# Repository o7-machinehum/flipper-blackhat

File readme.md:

# Flipper Blackhat

The Flipper Blackhat is a Linux based Flipper addon that enables WiFi attacks. It uses an Allwinner A33, which is a quad-core SoC connected to 512MB of RAM. The board has two USB2 ports, and one USB-C, which is connected to an FTDI.

## Software
There are three main repositories for this device.
- [The OS](https://github.com/o7-machinehum/flipper-blackhat-os)
- [The Flipper App](https://github.com/o7-machinehum/flipper-blackhat-app)
- This one (the hardware)

## License
The project is licensed under the Creative Commons (4.0 International License) Attribution—Noncommercial—Share Alike license. This allows sharing and adapting material for non-commercial purposes, provided credit is given to the creator and adaptations are shared under the same terms. The material can be used in any format with necessary technical modifications, but no warranties are provided. The license prohibits imposing additional restrictions and ensures the rights are irrevocable as long as the terms are followed.

Basically... If you make boards for yourself: great, make boards for your friends: great, but **please do not sell hundreds on them on Aliexpress**. I'm selling boards [here](https://shop.rootkitlabs.com/products/flipper-blackhat); the money made here goes back into this project and other similar open-source projects!

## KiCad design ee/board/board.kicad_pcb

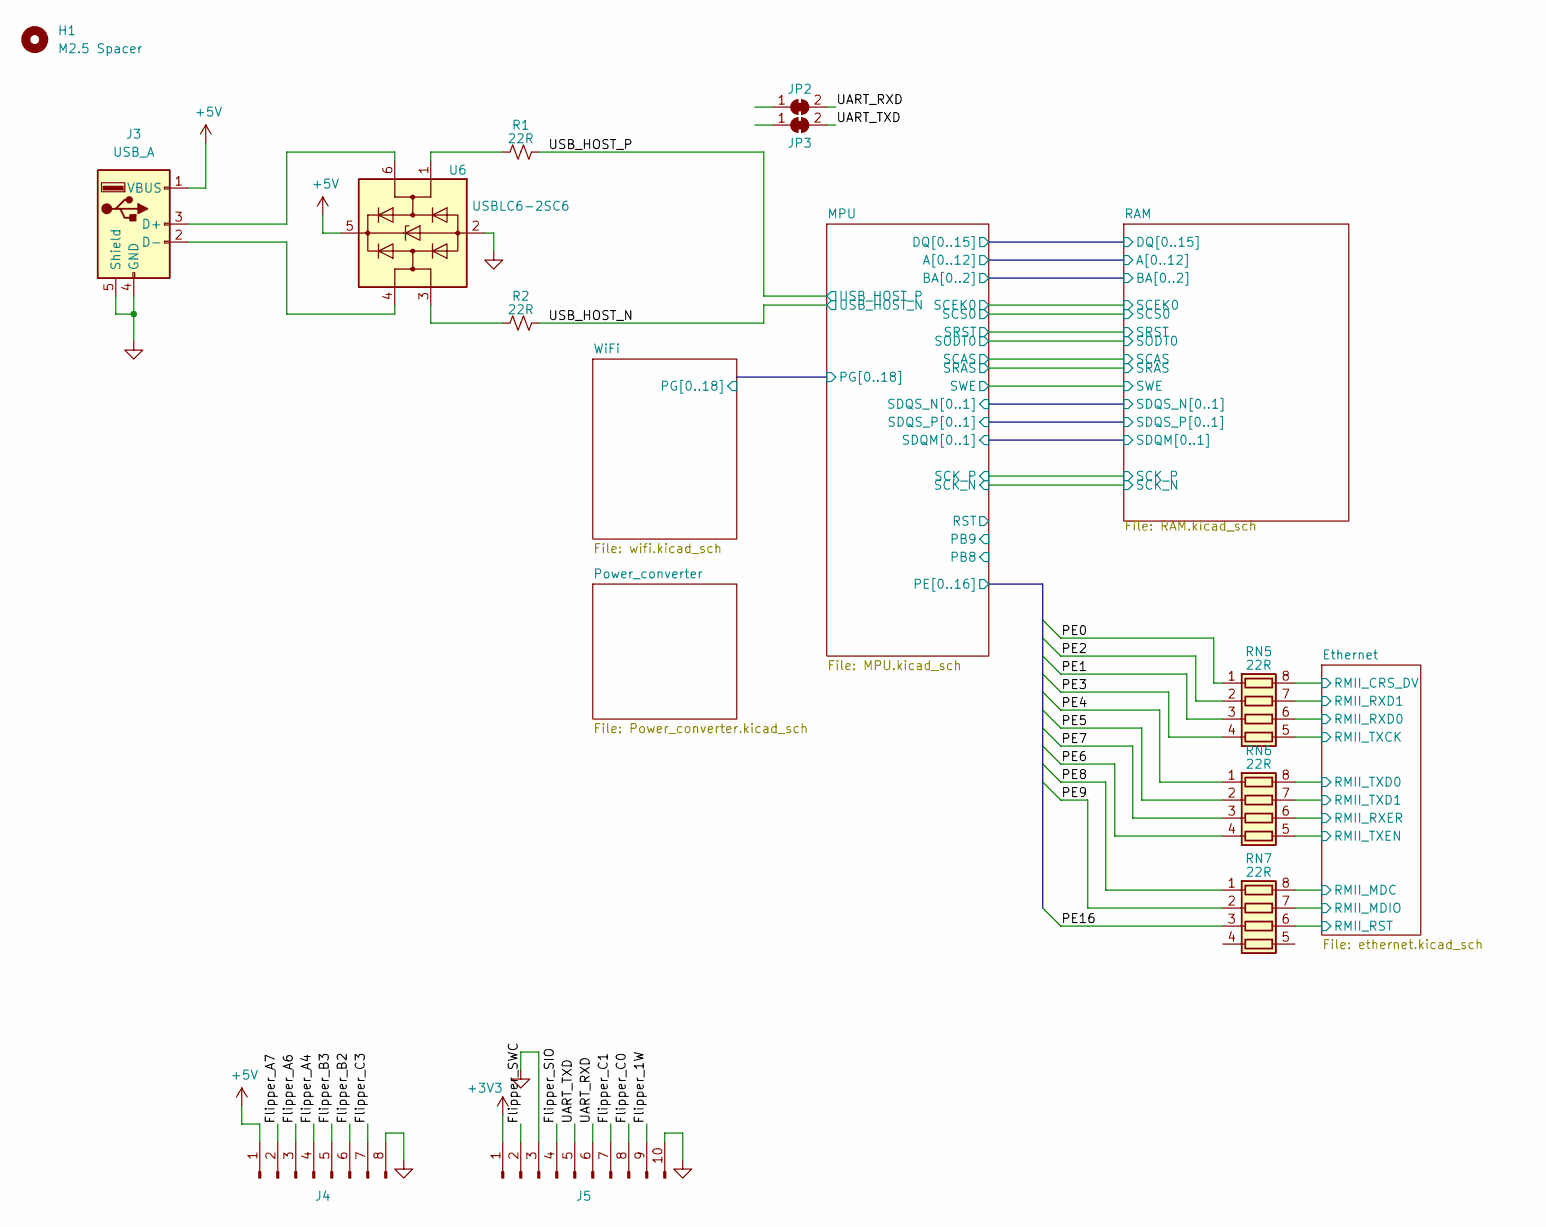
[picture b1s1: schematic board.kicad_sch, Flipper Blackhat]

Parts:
H1: M2.5 Spacer; 9774025151R; MPN 9774025151R
J3: USB_A; USB_A_Receptacle_GCT_USB1046; MPN USB1046-GF-0190-L-B-A
J4: Conn_01x08_Pin; PinHeader_1x08_P2.54mm_Horizontal; MPN PH1RB-08-UA
J5: Conn_01x10_Pin; PinHeader_1x10_P2.54mm_Horizontal; MPN PH1RB-10-UA
JP2, JP3: SolderJumper_2_Bridged; SolderJumper-2_P1.3mm_Bridged2Bar_RoundedPad1.0x1.5mm
R1, R2: 22R; R_0603_1608Metric; MPN RC0603FR-1322RL
RN5, RN6, RN7: 22R; R_Array_Convex_4x0402; MPN 4D02WGJ0220TCE
U6: USBLC6-2SC6; SOT-23-6; MPN USBLC6-2SC6

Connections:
+3V3: J5.1; also elsewhere on the board
+5V: J3.1 (VBUS), J4.1, U6.5 (VBUS); also elsewhere on the board
/Ethernet/RMII_CRS_DV: RN5.8 (R1.2); also elsewhere on the board
/Ethernet/RMII_MDC: RN7.8 (R1.2); also elsewhere on the board
/Ethernet/RMII_MDIO: RN7.7 (R2.2); also elsewhere on the board
/Ethernet/RMII_RXD0: RN5.6 (R3.2); also elsewhere on the board
/Ethernet/RMII_RXD1: RN5.7 (R2.2); also elsewhere on the board
/Ethernet/RMII_RXER: RN6.6 (R3.2); also elsewhere on the board
/Ethernet/RMII_TXCK: RN5.5 (R4.2); also elsewhere on the board
/Ethernet/RMII_TXD0: RN6.8 (R1.2); also elsewhere on the board
/Ethernet/RMII_TXD1: RN6.7 (R2.2); also elsewhere on the board
/Ethernet/RMII_TXEN: RN6.5 (R4.2); also elsewhere on the board
/Ethernet/RST: RN7.6 (R3.2); also elsewhere on the board
/Flipper_1W: J5.9
/Flipper_A4: J4.4
/Flipper_A6: J4.3
/Flipper_A7: J4.2
/Flipper_B2: J4.6
/Flipper_B3: J4.5
/Flipper_C0: J5.8
/Flipper_C1: J5.7
/Flipper_C3: J4.7
/Flipper_SIO: J5.4
/Flipper_SWC: J5.2
/MPU/PE0: RN5.1 (R1.1); also elsewhere on the board
/MPU/PE1: RN5.3 (R3.1); also elsewhere on the board
/MPU/PE2: RN5.2 (R2.1); also elsewhere on the board
/MPU/PE3: RN5.4 (R4.1); also elsewhere on the board
/MPU/PE4: RN6.1 (R1.1); also elsewhere on the board
/MPU/PE5: RN6.2 (R2.1); also elsewhere on the board
/MPU/PE6: RN6.4 (R4.1); also elsewhere on the board
/MPU/PE7: RN6.3 (R3.1); also elsewhere on the board
/MPU/PE8: RN7.1 (R1.1); also elsewhere on the board
/MPU/PE9: RN7.2 (R2.1); also elsewhere on the board
/MPU/PE16: RN7.3 (R3.1); also elsewhere on the board
/UART_RXD: J5.6, JP2.2 (B)
/UART_TXD: J5.5, JP3.2 (B)
/USB_HOST_N: R2.2; also elsewhere on the board
/USB_HOST_P: R1.2; also elsewhere on the board
GND: J3.4 (GND), J3.5 (Shield), J4.8, J5.3, J5.10, U6.2 (GND); also elsewhere on the board
unnamed: J3.3 (D+), U6.6 (I/O1)
unnamed: J3.2 (D-), U6.4 (I/O2)
unnamed: R1.1, U6.1 (I/O1)
unnamed: R2.1, U6.3 (I/O2)

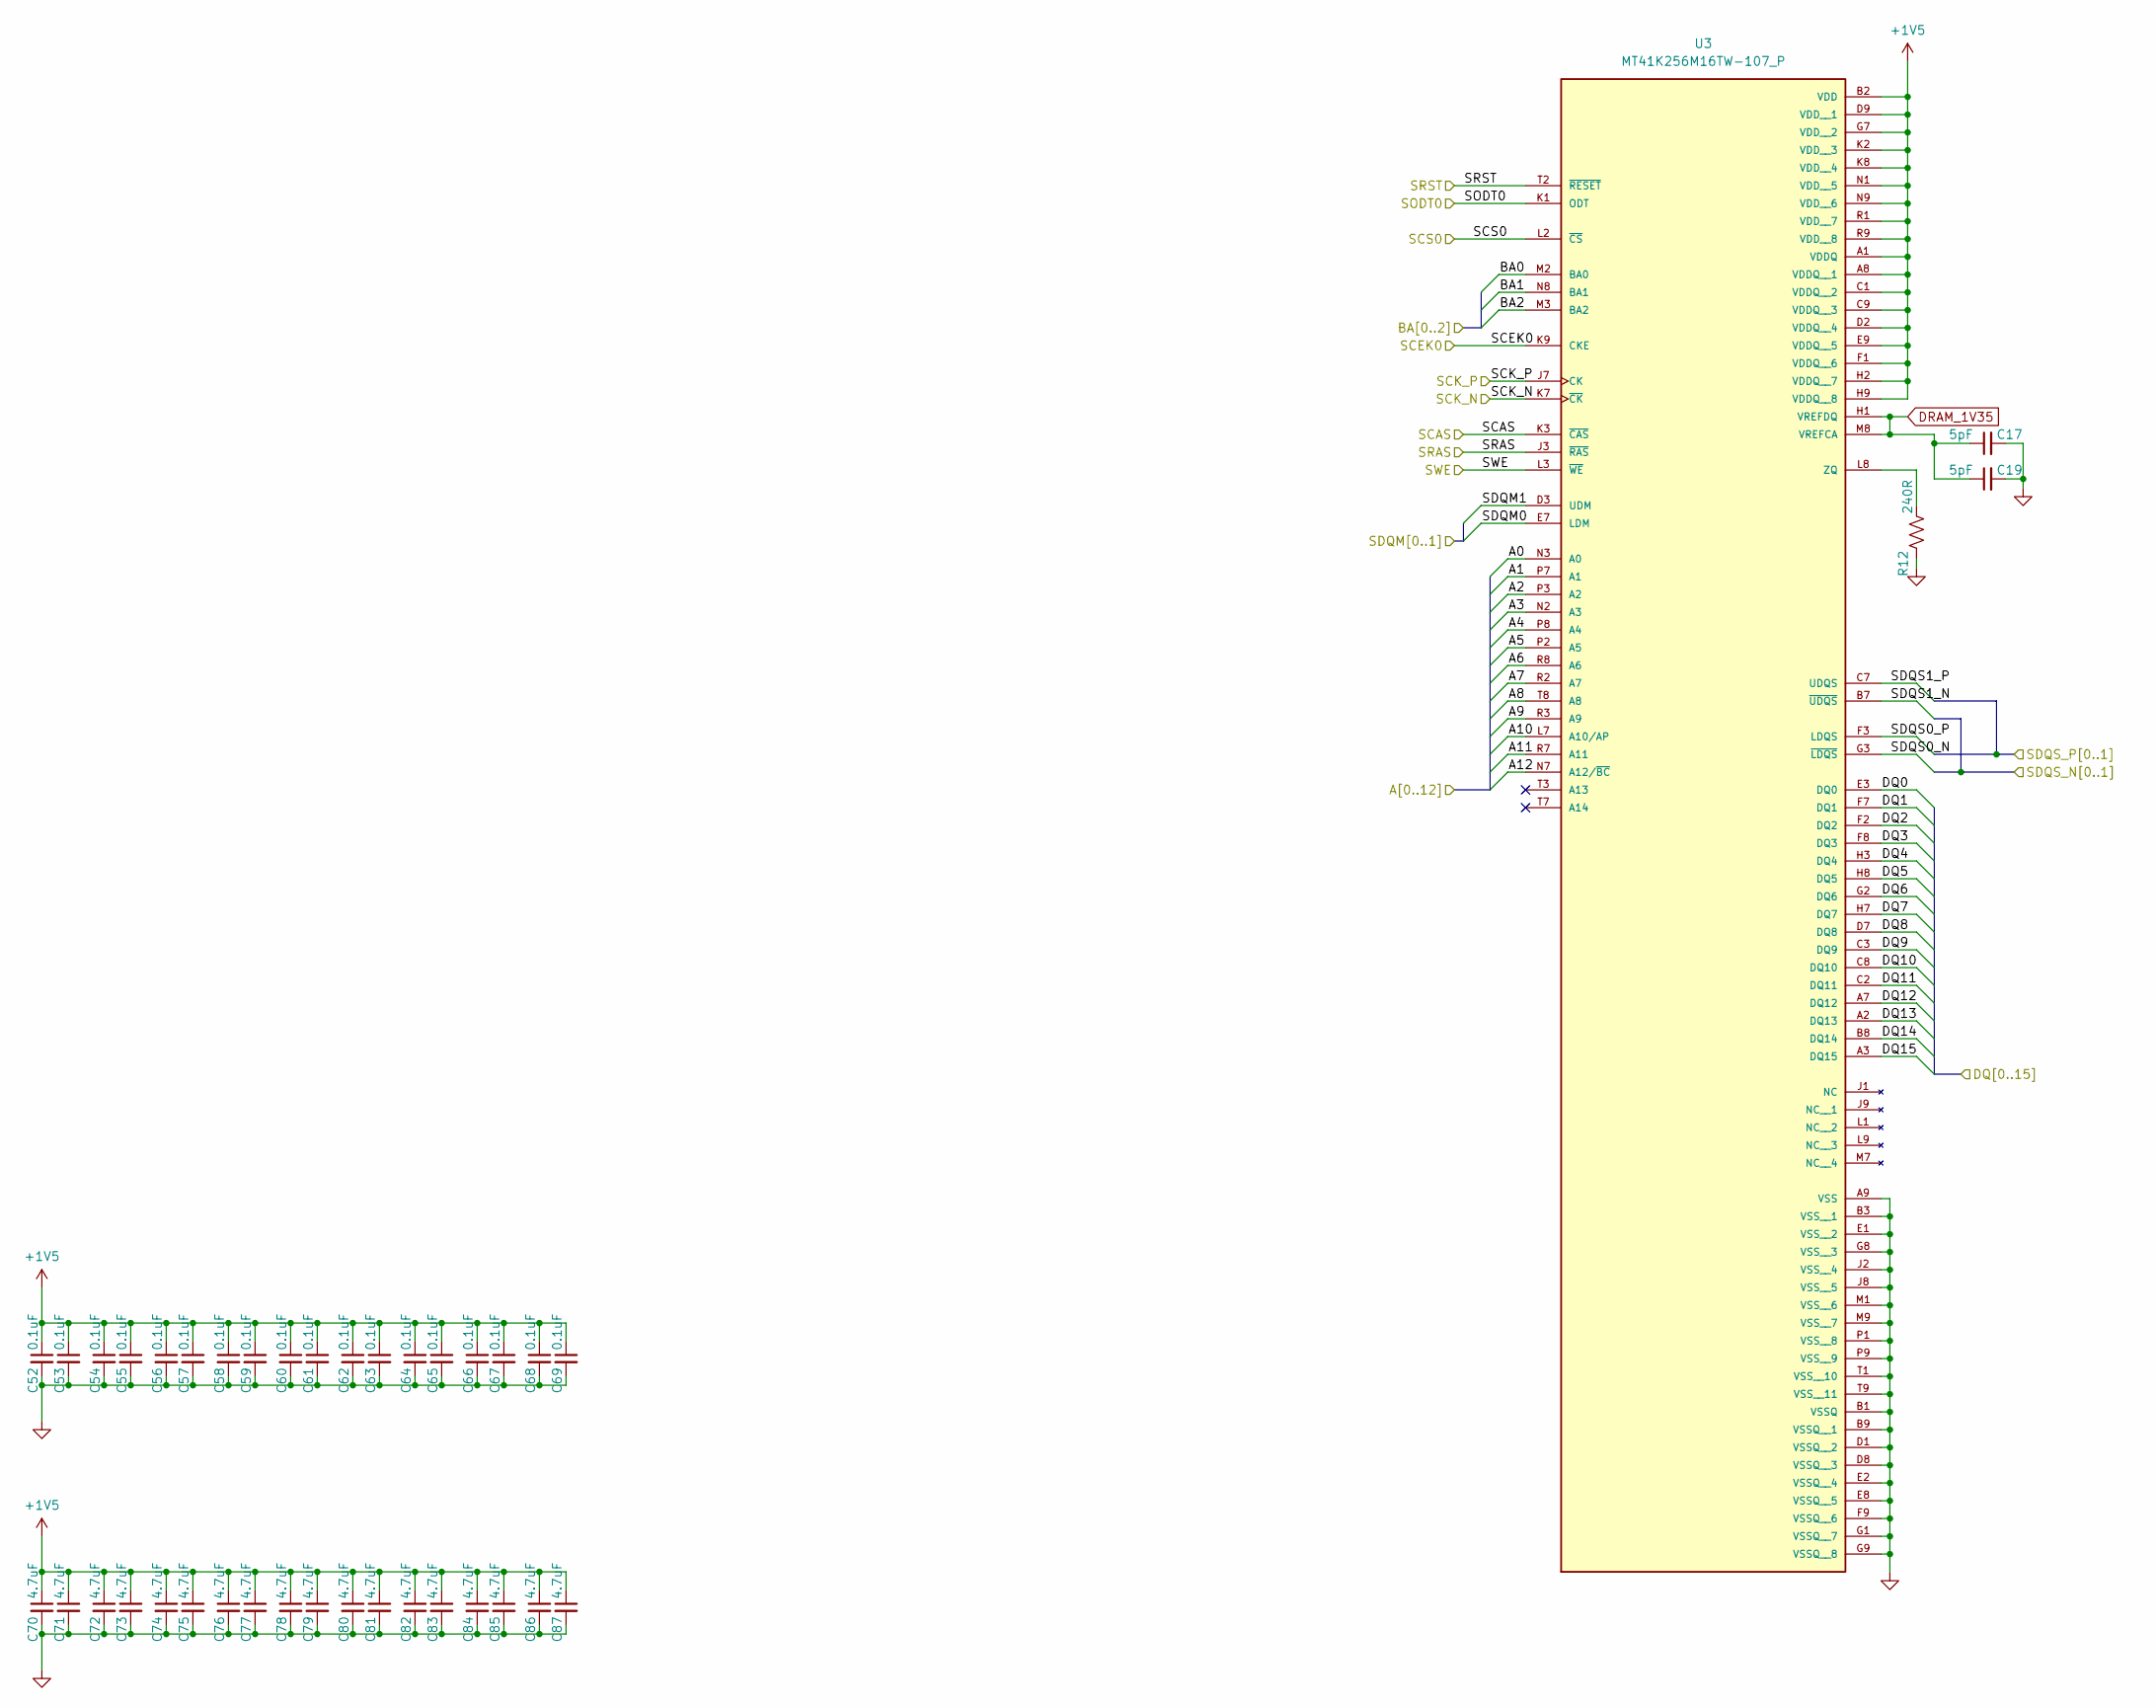
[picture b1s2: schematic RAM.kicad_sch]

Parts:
C17, C19: 5PF 50V C0G/NP0 0603; C_0603_1608Metric; MPN CL10C050CB81PNC
C52, C53, C54, C55, C56, C57, C58, C59, C60, C61, C62, C63, C64, C65, C66, C67, C68, C69: 16V 0.1uF X7R 0402; C_0402_1005Metric; MPN MLASE105SB7104KFNA01
C70, C71, C72, C73, C74, C75, C76, C77, C78, C79, C80, C81, C82, C83, C84, C85, C86, C87: 4.7 uF 16V 0805 X7R; C_0402_1005Metric; MPN C0805C475K4RACAUTO
R12: 240R; R_0603_1608Metric; MPN CRCW0603240RFKEAC
U3: MT41K256M16TW-107_P; BGA96C80P9X16_1400X800X120; PARTREV P

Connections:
+1V5: C52.1, C53.1, C54.1, C55.1, C56.1, C57.1, C58.1, C59.1, C60.1, C61.1, C62.1, C63.1, C64.1, C65.1, C66.1, C67.1, C68.1, C69.1, C70.1, C71.1, C72.1, C73.1, C74.1, C75.1, C76.1, C77.1, C78.1, C79.1, C80.1, C81.1, C82.1, C83.1, C84.1, C85.1, C86.1, C87.1, U3.A1 (VDDQ), U3.A8 (VDDQ__1), U3.B2 (VDD), U3.C1 (VDDQ__2), U3.C9 (VDDQ__3), U3.D2 (VDDQ__4), U3.D9 (VDD__1), U3.E9 (VDDQ__5), U3.F1 (VDDQ__6), U3.G7 (VDD__2), U3.H2 (VDDQ__7), U3.H9 (VDDQ__8), U3.K2 (VDD__3), U3.K8 (VDD__4), U3.N1 (VDD__5), U3.N9 (VDD__6), U3.R1 (VDD__7), U3.R9 (VDD__8); also elsewhere on the board
/MPU/A0: U3.N3 (A0); also elsewhere on the board
/MPU/A1: U3.P7 (A1); also elsewhere on the board
/MPU/A2: U3.P3 (A2); also elsewhere on the board
/MPU/A3: U3.N2 (A3); also elsewhere on the board
/MPU/A4: U3.P8 (A4); also elsewhere on the board
/MPU/A5: U3.P2 (A5); also elsewhere on the board
/MPU/A6: U3.R8 (A6); also elsewhere on the board
/MPU/A7: U3.R2 (A7); also elsewhere on the board
/MPU/A8: U3.T8 (A8); also elsewhere on the board
/MPU/A9: U3.R3 (A9); also elsewhere on the board
/MPU/A10: U3.L7 (A10/AP); also elsewhere on the board
/MPU/A11: U3.R7 (A11); also elsewhere on the board
/MPU/A12: U3.N7 (A12/~BC); also elsewhere on the board
/MPU/BA0: U3.M2 (BA0); also elsewhere on the board
/MPU/BA1: U3.N8 (BA1); also elsewhere on the board
/MPU/BA2: U3.M3 (BA2); also elsewhere on the board
/MPU/DQ0: U3.E3 (DQ0); also elsewhere on the board
/MPU/DQ1: U3.F7 (DQ1); also elsewhere on the board
/MPU/DQ2: U3.F2 (DQ2); also elsewhere on the board
/MPU/DQ3: U3.F8 (DQ3); also elsewhere on the board
/MPU/DQ4: U3.H3 (DQ4); also elsewhere on the board
/MPU/DQ5: U3.H8 (DQ5); also elsewhere on the board
/MPU/DQ6: U3.G2 (DQ6); also elsewhere on the board
/MPU/DQ7: U3.H7 (DQ7); also elsewhere on the board
/MPU/DQ8: U3.D7 (DQ8); also elsewhere on the board
/MPU/DQ9: U3.C3 (DQ9); also elsewhere on the board
/MPU/DQ10: U3.C8 (DQ10); also elsewhere on the board
/MPU/DQ11: U3.C2 (DQ11); also elsewhere on the board
/MPU/DQ12: U3.A7 (DQ12); also elsewhere on the board
/MPU/DQ13: U3.A2 (DQ13); also elsewhere on the board
/MPU/DQ14: U3.B8 (DQ14); also elsewhere on the board
/MPU/DQ15: U3.A3 (DQ15); also elsewhere on the board
/MPU/SCAS: U3.K3 (~CAS); also elsewhere on the board
/MPU/SCEK0: U3.K9 (CKE); also elsewhere on the board
/MPU/SCK_N: U3.K7 (~CK); also elsewhere on the board
/MPU/SCK_P: U3.J7 (CK); also elsewhere on the board
/MPU/SCS0: U3.L2 (~CS); also elsewhere on the board
/MPU/SDQM0: U3.E7 (LDM); also elsewhere on the board
/MPU/SDQM1: U3.D3 (UDM); also elsewhere on the board
/MPU/SODT0: U3.K1 (ODT); also elsewhere on the board
/MPU/SRAS: U3.J3 (~RAS); also elsewhere on the board
/MPU/SRST: U3.T2 (~RESET); also elsewhere on the board
/MPU/SWE: U3.L3 (~WE); also elsewhere on the board
/RAM/SDQS0_N: U3.G3 (~LDQS)
/RAM/SDQS0_P: U3.F3 (LDQS)
/RAM/SDQS1_N: U3.B7 (~UDQS)
/RAM/SDQS1_P: U3.C7 (UDQS)
DRAM_1V35: C17.1, C19.1, U3.H1 (VREFDQ), U3.M8 (VREFCA); also elsewhere on the board
GND: C17.2, C19.2, C52.2, C53.2, C54.2, C55.2, C56.2, C57.2, C58.2, C59.2, C60.2, C61.2, C62.2, C63.2, C64.2, C65.2, C66.2, C67.2, C68.2, C69.2, C70.2, C71.2, C72.2, C73.2, C74.2, C75.2, C76.2, C77.2, C78.2, C79.2, C80.2, C81.2, C82.2, C83.2, C84.2, C85.2, C86.2, C87.2, R12.1, U3.A9 (VSS), U3.B1 (VSSQ), U3.B3 (VSS__1), U3.B9 (VSSQ__1), U3.D1 (VSSQ__2), U3.D8 (VSSQ__3), U3.E1 (VSS__2), U3.E2 (VSSQ__4), U3.E8 (VSSQ__5), U3.F9 (VSSQ__6), U3.G1 (VSSQ__7), U3.G8 (VSS__3), U3.G9 (VSSQ__8), U3.J2 (VSS__4), U3.J8 (VSS__5), U3.M1 (VSS__6), U3.M9 (VSS__7), U3.P1 (VSS__8), U3.P9 (VSS__9), U3.T1 (VSS__10), U3.T9 (VSS__11); also elsewhere on the board
unnamed: R12.2, U3.L8 (ZQ)

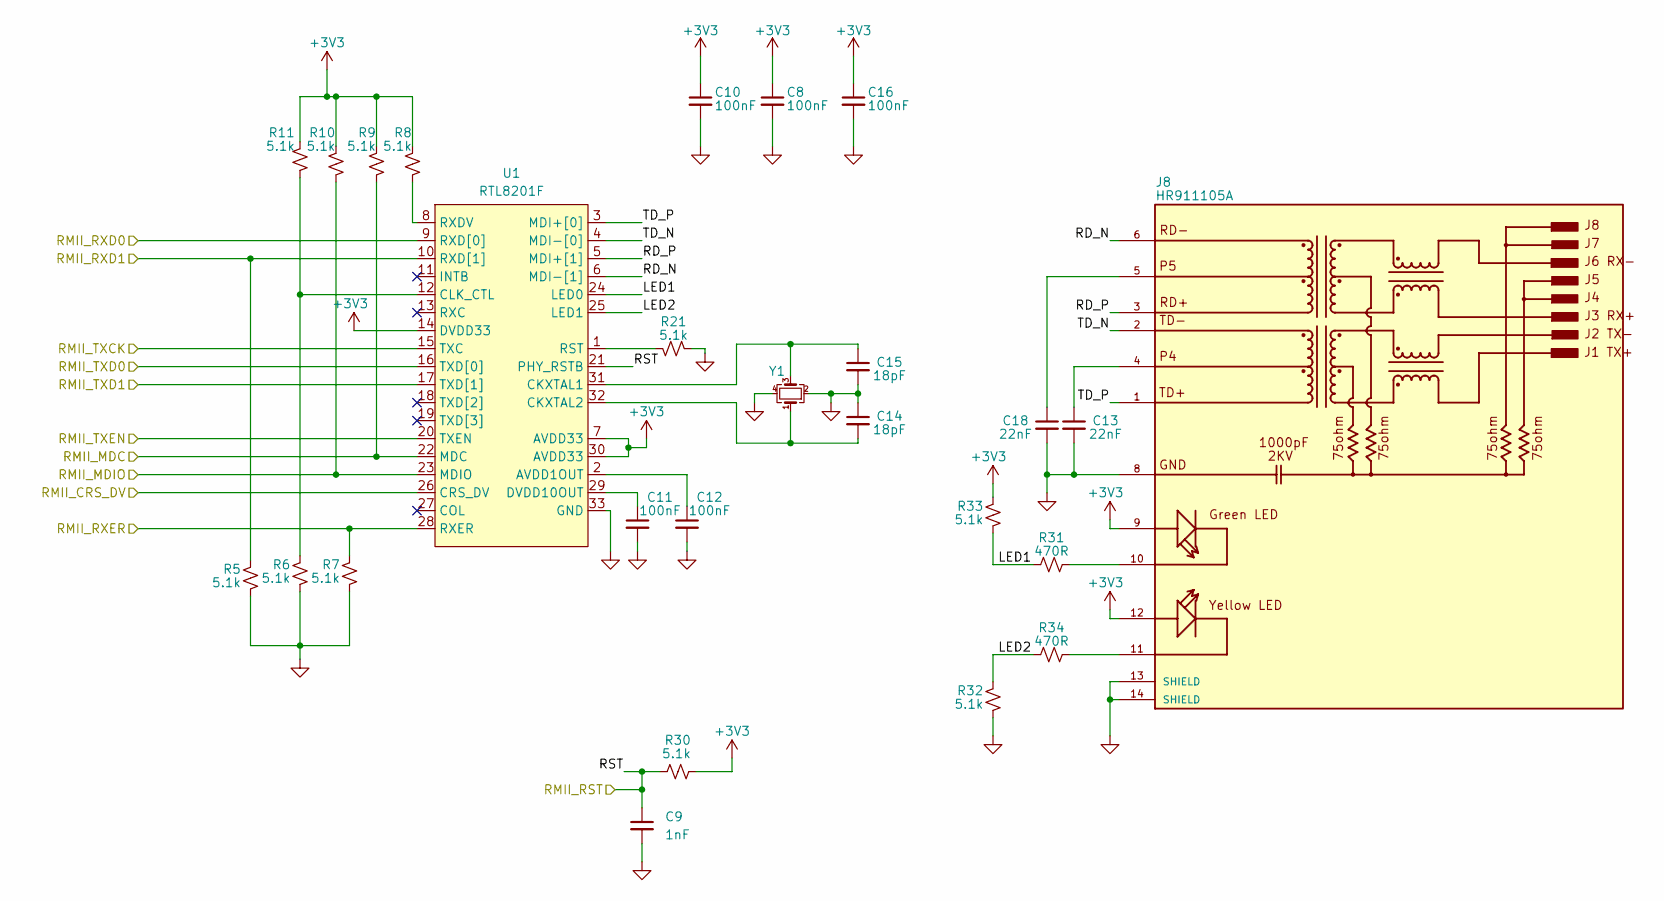
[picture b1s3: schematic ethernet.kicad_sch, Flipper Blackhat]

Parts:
C8, C10, C11, C12, C16: 100nF; C_0603_1608Metric; MPN CC0603KRX7R7BB104
C9: 1nF; C_0603_1608Metric; MPN CC0603KRX7R7BB102
C13, C18: 22nF; C_0603_1608Metric; MPN CC0603KRX7R7BB223
C14, C15: 18pF; C_0603_1608Metric; MPN CC0603JPNPO9BN180
J8: HR911105A; HR911105a; MPN HR911105A
R5, R6, R7, R8, R9, R10, R11, R21, R30, R32, R33: 5.1k; R_0603_1608Metric; MPN RC0603FR-135K1L
R31, R34: 470R; R_0603_1608Metric; MPN RC0603FR-13470KL
U1: RTL8201F; QFN-32-1EP_5x5mm_P0.5mm_EP3.3x3.3mm; MPN RTL8201F
Y1: Crystal_GND24_Small; Crystal_SMD_3225-4Pin_3.2x2.5mm; MPN 7M25000033

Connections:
+3V3: C8.1, C10.1, C16.1, J8.9, J8.12, R8.2, R9.2, R10.2, R11.2, R30.1, R33.2, U1.7 (AVDD33), U1.14 (DVDD33), U1.30 (AVDD33); also elsewhere on the board
/Ethernet/LED1: R31.2, R33.1, U1.24 (LED0)
/Ethernet/LED2: R32.2, R34.2, U1.25 (LED1)
/Ethernet/RD_N: J8.6, U1.6 (MDI-[1])
/Ethernet/RD_P: J8.3, U1.5 (MDI+[1])
/Ethernet/RMII_CRS_DV: U1.26 (CRS_DV); also elsewhere on the board
/Ethernet/RMII_MDC: R9.1, U1.22 (MDC); also elsewhere on the board
/Ethernet/RMII_MDIO: R10.1, U1.23 (MDIO); also elsewhere on the board
/Ethernet/RMII_RXD0: U1.9 (RXD[0]); also elsewhere on the board
/Ethernet/RMII_RXD1: R5.2, U1.10 (RXD[1]); also elsewhere on the board
/Ethernet/RMII_RXER: R7.2, U1.28 (RXER); also elsewhere on the board
/Ethernet/RMII_TXCK: U1.15 (TXC); also elsewhere on the board
/Ethernet/RMII_TXD0: U1.16 (TXD[0]); also elsewhere on the board
/Ethernet/RMII_TXD1: U1.17 (TXD[1]); also elsewhere on the board
/Ethernet/RMII_TXEN: U1.20 (TXEN); also elsewhere on the board
/Ethernet/RST: C9.1, R30.2, U1.21 (PHY_RSTB); also elsewhere on the board
/Ethernet/TD_N: J8.2, U1.4 (MDI-[0])
/Ethernet/TD_P: J8.1, U1.3 (MDI+[0])
GND: C8.2, C9.2, C10.2, C11.2, C12.2, C13.2, C14.1, C15.2, C16.2, C18.2, J8.8, J8.13 (SHIELD), J8.14 (SHIELD), R5.1, R6.1, R7.1, R21.2, R32.1, U1.33 (GND), Y1.2, Y1.4; also elsewhere on the board
unnamed: C13.1, J8.4
unnamed: C18.1, J8.5
unnamed: J8.10, R31.1
unnamed: J8.11, R34.1
unnamed: C12.1, U1.2 (AVDD1OUT)
unnamed: C15.1, U1.31 (CKXTAL1), Y1.3
unnamed: C14.2, U1.32 (CKXTAL2), Y1.1
unnamed: R6.2, R11.1, U1.12 (CLK_CTL)
unnamed: C11.1, U1.29 (DVDD10OUT)
unnamed: R21.1, U1.1 (RST)
unnamed: R8.1, U1.8 (RXDV)

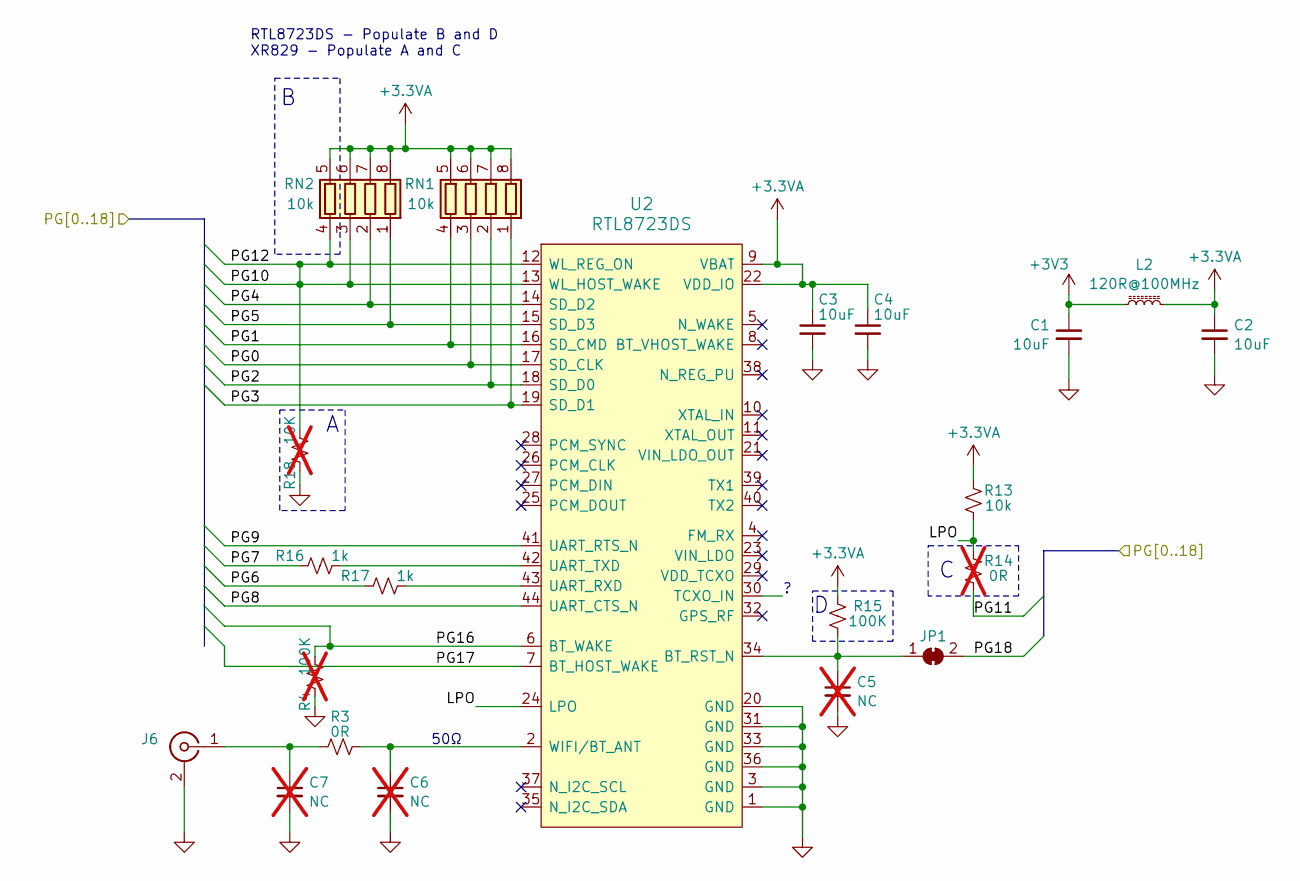
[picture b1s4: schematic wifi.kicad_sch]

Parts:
C1, C2, C3, C4: 10uF; C_0603_1608Metric; MPN LMK107BBJ106MALT
C5, C6, C7: NC; C_0603_1608Metric; not fitted
J6: Conn_Coaxial; SMA_Amphenol_901-143_Horizontal; MPN 901-143-6RFX
JP1: SolderJumper_2_Bridged; SolderJumper-2_P1.3mm_Bridged2Bar_RoundedPad1.0x1.5mm
L2: 120R@100MHz; R_0805_2012Metric; MPN MMZ2012R121AT000
R3: 0R; R_0603_1608Metric; MPN RC0603FR-130RL
R4: 100K; R_0603_1608Metric; not fitted
R13: 10k; R_0603_1608Metric; MPN RC0603FR-1310KL
R14: 0R; R_0603_1608Metric; not fitted
R15: 100K; R_0603_1608Metric; MPN RC0603FR-13100KL
R16, R17: 1k; R_0603_1608Metric; MPN RC0603FR-131KL
R18: 10K; R_0603_1608Metric; not fitted
RN1, RN2: 10k; R_Array_Convex_4x0402; MPN 4D02WGJ0103TCE
U2: RTL8723DS; RTL8723; MPN RTL8723DS

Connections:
+3.3VA: C2.1, C3.1, C4.1, L2.2, R13.2, R15.2, RN1.5 (R4.2), RN1.6 (R3.2), RN1.7 (R2.2), RN1.8 (R1.2), RN2.5 (R4.2), RN2.6 (R3.2), RN2.7 (R2.2), RN2.8 (R1.2), U2.9 (VBAT), U2.22 (VDD_IO)
+3V3: C1.1, L2.1; also elsewhere on the board
/WiFi/LPO: R13.1, R14.2, U2.24 (LPO)
/WiFi/PG0: RN1.3 (R3.1), U2.17 (SD_CLK)
/WiFi/PG1: RN1.4 (R4.1), U2.16 (SD_CMD)
/WiFi/PG2: RN1.2 (R2.1), U2.18 (SD_D0)
/WiFi/PG3: RN1.1 (R1.1), U2.19 (SD_D1)
/WiFi/PG4: RN2.2 (R2.1), U2.14 (SD_D2)
/WiFi/PG5: RN2.1 (R1.1), U2.15 (SD_D3)
/WiFi/PG6: R17.1
/WiFi/PG7: R16.1
/WiFi/PG8: U2.44 (UART_CTS_N)
/WiFi/PG9: U2.41 (UART_RTS_N)
/WiFi/PG10: R18.2, RN2.3 (R3.1), RN2.4 (R4.1), U2.12 (WL_REG_ON), U2.13 (WL_HOST_WAKE)
/WiFi/PG11: R14.1
/WiFi/PG16: R4.2, U2.6 (BT_WAKE)
/WiFi/PG17: U2.7 (BT_HOST_WAKE)
/WiFi/PG18: JP1.2 (B)
GND: C1.2, C2.2, C3.2, C4.2, C5.2, C6.2, C7.2, J6.2 (Ext), R4.1, R18.1, U2.1 (GND), U2.3 (GND), U2.20 (GND), U2.31 (GND), U2.33 (GND), U2.36 (GND); also elsewhere on the board
unnamed: C7.1, J6.1 (In), R3.1
unnamed: C5.1, JP1.1 (A), R15.1, U2.34 (BT_RST_N)
unnamed: R17.2, U2.43 (UART_RXD)
unnamed: R16.2, U2.42 (UART_TXD)
unnamed: C6.1, R3.2, U2.2 (WIFI/BT_ANT)

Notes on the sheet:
RTL8723DS - Populate B and D XR829 - Populate A and C
50Ω

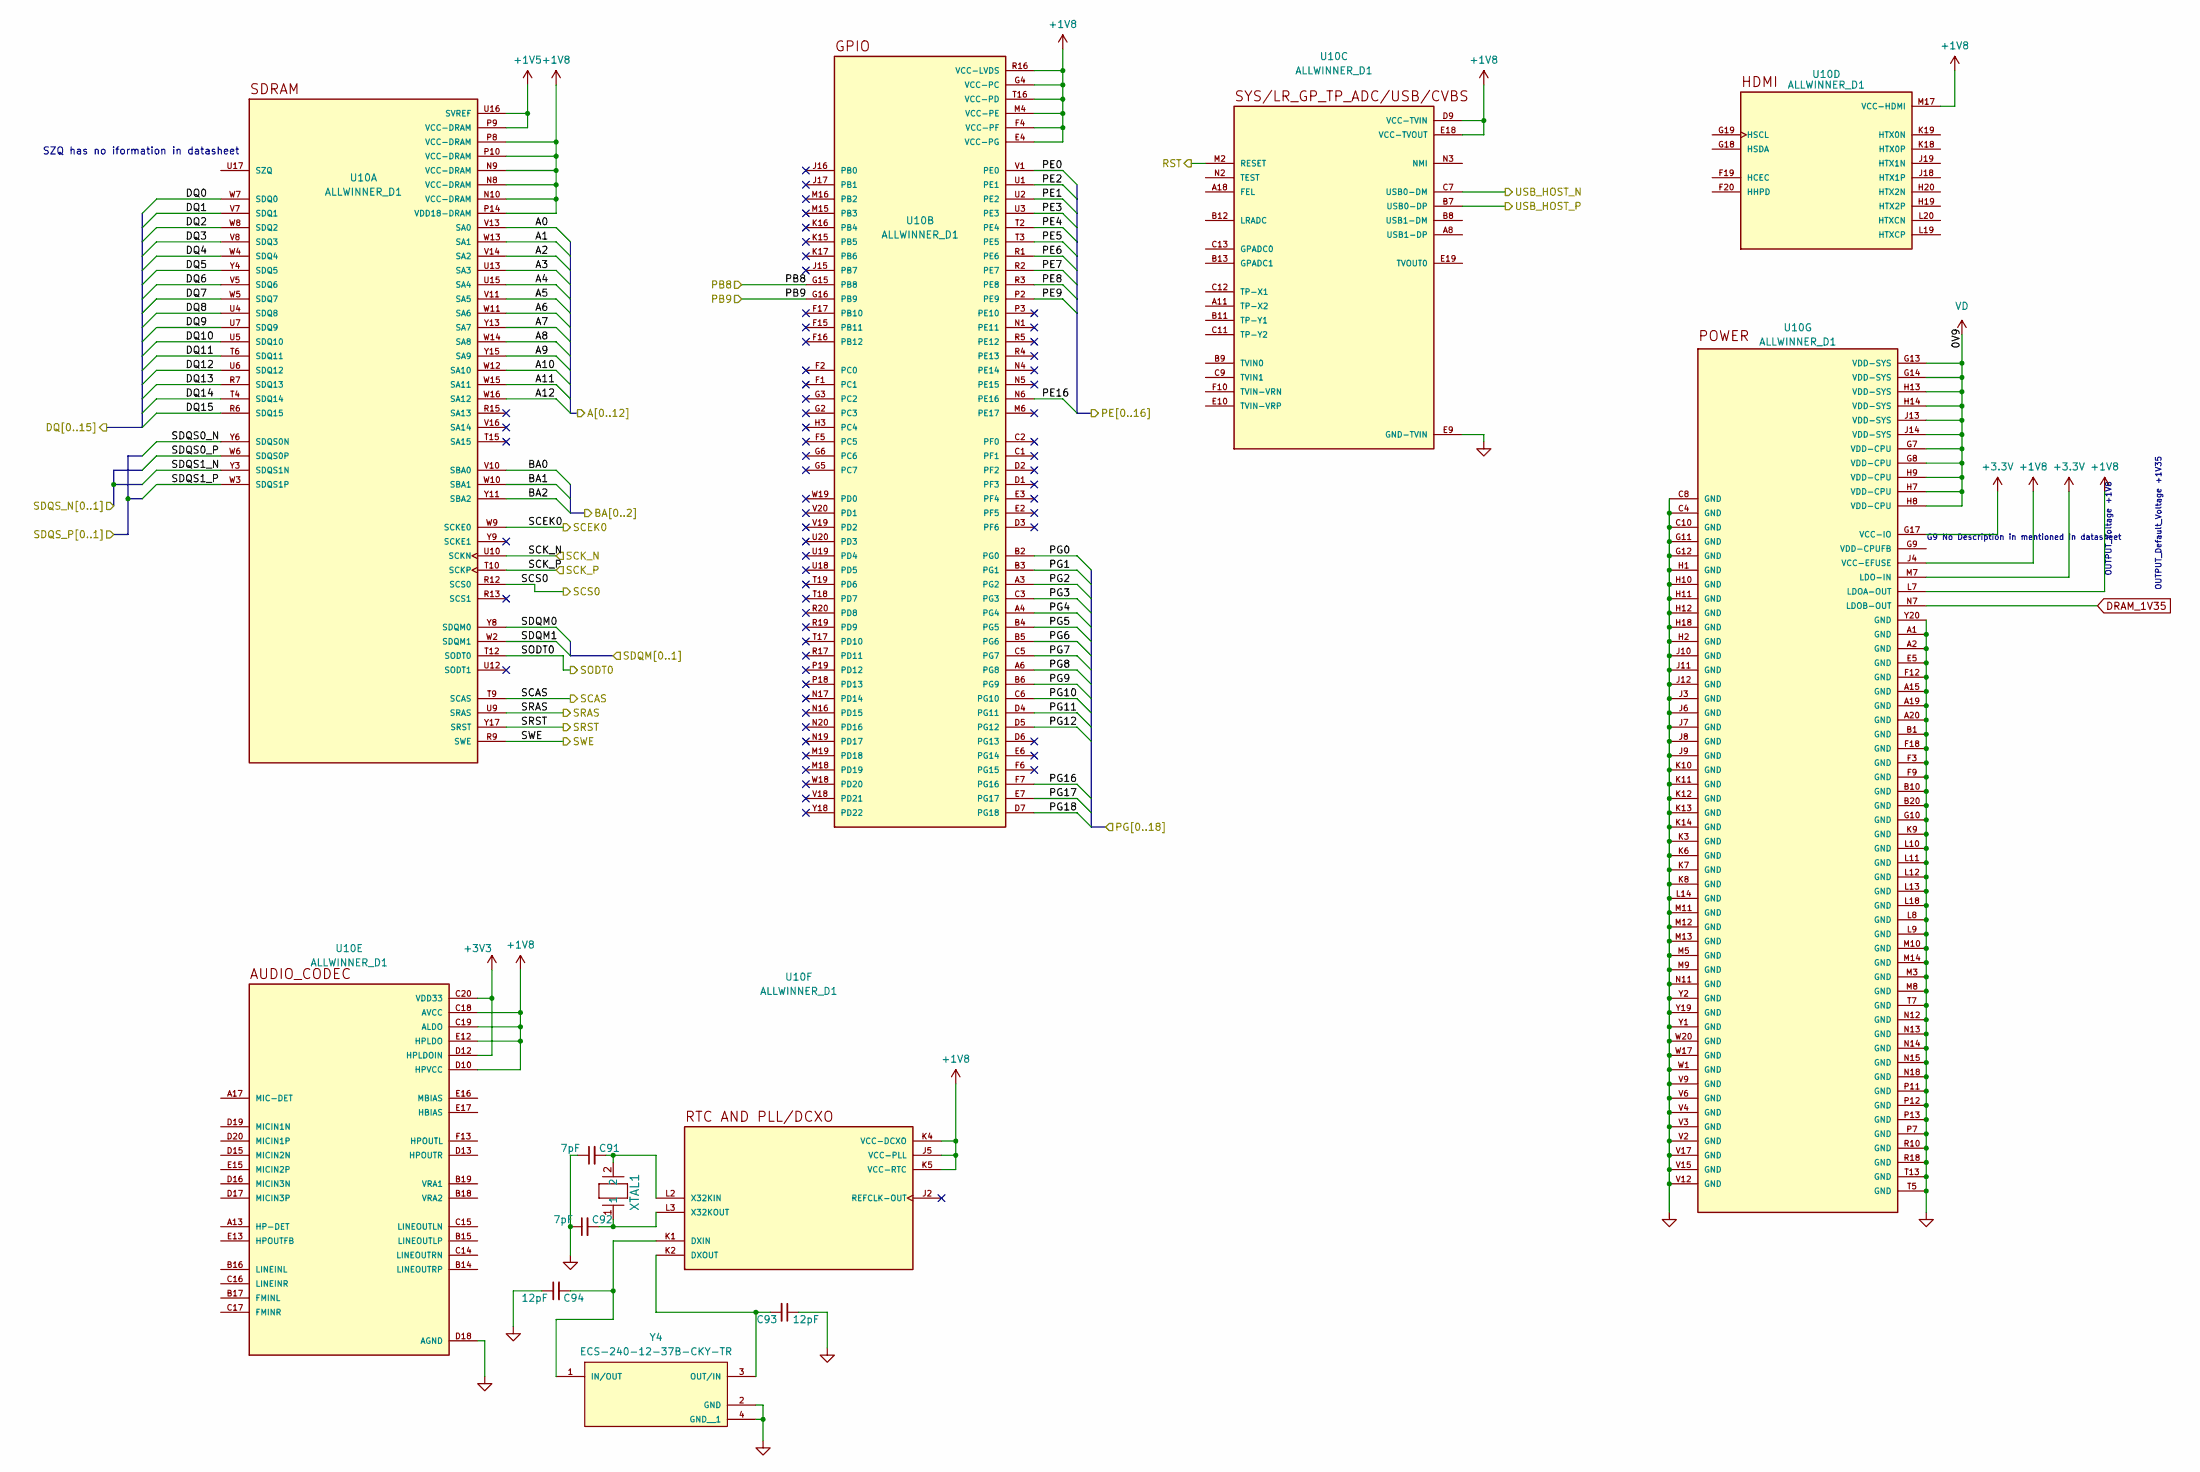
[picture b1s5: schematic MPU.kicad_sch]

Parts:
C91, C92: 7PF 50V C0G/NP0 0603; C_0402_1005Metric; MPN CL10C070CB8NNNC
C93, C94: 12PF 50V C0G/NP0; C_0402_1005Metric; MPN GJM1555C1H120FB01D
U10: ALLWINNER_D1; BGA337C65P20X20_1300X1300X133
XTAL1: SC32S-7PF20PPM; Crystal_SMD_TXC_7A-2Pin_5x3.2mm
Y4: ECS-240-12-37B-CKY-TR; XTAL_ECS-240-12-37B-CKY-TR

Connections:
+1V5: U10.P9 (VCC-DRAM), U10.U16 (SVREF); also elsewhere on the board
+1V8: U10.C18 (AVCC), U10.C19 (ALDO), U10.D9 (VCC-TVIN), U10.D10 (HPVCC), U10.E4 (VCC-PG), U10.E12 (HPLDO), U10.E18 (VCC-TVOUT), U10.F4 (VCC-PF), U10.G4 (VCC-PC), U10.J4 (VCC-EFUSE), U10.J5 (VCC-PLL), U10.K4 (VCC-DCXO), U10.K5 (VCC-RTC), U10.L7 (LDOA-OUT), U10.M4 (VCC-PE), U10.M17 (VCC-HDMI), U10.N8 (VCC-DRAM), U10.N9 (VCC-DRAM), U10.N10 (VCC-DRAM), U10.P8 (VCC-DRAM), U10.P10 (VCC-DRAM), U10.P14 (VDD18-DRAM), U10.R16 (VCC-LVDS), U10.T16 (VCC-PD)
+3.3V: U10.G17 (VCC-IO), U10.M7 (LDO-IN); also elsewhere on the board
+3V3: U10.C20 (VDD33), U10.D12 (HPLDOIN); also elsewhere on the board
/MPU/A0: U10.V13 (SA0); also elsewhere on the board
/MPU/A1: U10.W13 (SA1); also elsewhere on the board
/MPU/A2: U10.V14 (SA2); also elsewhere on the board
/MPU/A3: U10.U13 (SA3); also elsewhere on the board
/MPU/A4: U10.U15 (SA4); also elsewhere on the board
/MPU/A5: U10.V11 (SA5); also elsewhere on the board
/MPU/A6: U10.W11 (SA6); also elsewhere on the board
/MPU/A7: U10.Y13 (SA7); also elsewhere on the board
/MPU/A8: U10.W14 (SA8); also elsewhere on the board
/MPU/A9: U10.Y15 (SA9); also elsewhere on the board
/MPU/A10: U10.W12 (SA10); also elsewhere on the board
/MPU/A11: U10.W15 (SA11); also elsewhere on the board
/MPU/A12: U10.W16 (SA12); also elsewhere on the board
/MPU/BA0: U10.V10 (SBA0); also elsewhere on the board
/MPU/BA1: U10.W10 (SBA1); also elsewhere on the board
/MPU/BA2: U10.Y11 (SBA2); also elsewhere on the board
/MPU/DQ0: U10.W7 (SDQ0); also elsewhere on the board
/MPU/DQ1: U10.V7 (SDQ1); also elsewhere on the board
/MPU/DQ2: U10.W8 (SDQ2); also elsewhere on the board
/MPU/DQ3: U10.V8 (SDQ3); also elsewhere on the board
/MPU/DQ4: U10.W4 (SDQ4); also elsewhere on the board
/MPU/DQ5: U10.Y4 (SDQ5); also elsewhere on the board
/MPU/DQ6: U10.V5 (SDQ6); also elsewhere on the board
/MPU/DQ7: U10.W5 (SDQ7); also elsewhere on the board
/MPU/DQ8: U10.U4 (SDQ8); also elsewhere on the board
/MPU/DQ9: U10.U7 (SDQ9); also elsewhere on the board
/MPU/DQ10: U10.U5 (SDQ10); also elsewhere on the board
/MPU/DQ11: U10.T6 (SDQ11); also elsewhere on the board
/MPU/DQ12: U10.U6 (SDQ12); also elsewhere on the board
/MPU/DQ13: U10.R7 (SDQ13); also elsewhere on the board
/MPU/DQ14: U10.T4 (SDQ14); also elsewhere on the board
/MPU/DQ15: U10.R6 (SDQ15); also elsewhere on the board
/MPU/PB8: U10.G15 (PB8)
/MPU/PB9: U10.G16 (PB9)
/MPU/PE0: U10.V1 (PE0); also elsewhere on the board
/MPU/PE1: U10.U2 (PE2); also elsewhere on the board
/MPU/PE2: U10.U1 (PE1); also elsewhere on the board
/MPU/PE3: U10.U3 (PE3); also elsewhere on the board
/MPU/PE4: U10.T2 (PE4); also elsewhere on the board
/MPU/PE5: U10.T3 (PE5); also elsewhere on the board
/MPU/PE6: U10.R1 (PE6); also elsewhere on the board
/MPU/PE7: U10.R2 (PE7); also elsewhere on the board
/MPU/PE8: U10.R3 (PE8); also elsewhere on the board
/MPU/PE9: U10.P2 (PE9); also elsewhere on the board
/MPU/PE16: U10.N6 (PE16); also elsewhere on the board
/MPU/PG0: U10.B2 (PG0)
/MPU/PG1: U10.B3 (PG1)
/MPU/PG2: U10.A3 (PG2)
/MPU/PG3: U10.C3 (PG3)
/MPU/PG4: U10.A4 (PG4)
/MPU/PG5: U10.B4 (PG5)
/MPU/PG6: U10.B5 (PG6)
/MPU/PG7: U10.C5 (PG7)
/MPU/PG8: U10.A6 (PG8)
/MPU/PG9: U10.B6 (PG9)
/MPU/PG10: U10.C6 (PG10)
/MPU/PG11: U10.D4 (PG11)
/MPU/PG12: U10.D5 (PG12)
/MPU/PG16: U10.F7 (PG16)
/MPU/PG17: U10.E7 (PG17)
/MPU/PG18: U10.D7 (PG18)
/MPU/RST: U10.M2 (RESET)
/MPU/SCAS: U10.T9 (SCAS); also elsewhere on the board
/MPU/SCEK0: U10.W9 (SCKE0); also elsewhere on the board
/MPU/SCK_N: U10.U10 (SCKN); also elsewhere on the board
/MPU/SCK_P: U10.T10 (SCKP); also elsewhere on the board
/MPU/SCS0: U10.R12 (SCS0); also elsewhere on the board
/MPU/SDQM0: U10.Y8 (SDQM0); also elsewhere on the board
/MPU/SDQM1: U10.W2 (SDQM1); also elsewhere on the board
/MPU/SDQS0_N: U10.Y6 (SDQS0N)
/MPU/SDQS0_P: U10.W6 (SDQS0P)
/MPU/SDQS1_N: U10.Y3 (SDQS1N)
/MPU/SDQS1_P: U10.W3 (SDQS1P)
/MPU/SODT0: U10.T12 (SODT0); also elsewhere on the board
/MPU/SRAS: U10.U9 (SRAS); also elsewhere on the board
/MPU/SRST: U10.Y17 (SRST); also elsewhere on the board
/MPU/SWE: U10.R9 (SWE); also elsewhere on the board
/USB_HOST_N: U10.C7 (USB0-DM); also elsewhere on the board
/USB_HOST_P: U10.B7 (USB0-DP); also elsewhere on the board
DRAM_1V35: U10.N7 (LDOB-OUT); also elsewhere on the board
GND: C91.1, C92.1, C93.1, C94.1, U10.A1 (GND), U10.A2 (GND), U10.A15 (GND), U10.A19 (GND), U10.A20 (GND), U10.B1 (GND), U10.B10 (GND), U10.B20 (GND), U10.C4 (GND), U10.C8 (GND), U10.C10 (GND), U10.D18 (AGND), U10.E5 (GND), U10.E9 (GND-TVIN), U10.F3 (GND), U10.F9 (GND), U10.F12 (GND), U10.F18 (GND), U10.G10 (GND), U10.G11 (GND), U10.G12 (GND), U10.H1 (GND), U10.H2 (GND), U10.H10 (GND), U10.H11 (GND), U10.H12 (GND), U10.H18 (GND), U10.J3 (GND), U10.J6 (GND), U10.J7 (GND), U10.J8 (GND), U10.J9 (GND), U10.J10 (GND), U10.J11 (GND), U10.J12 (GND), U10.K3 (GND), U10.K6 (GND), U10.K7 (GND), U10.K8 (GND), U10.K9 (GND), U10.K10 (GND), U10.K11 (GND), U10.K12 (GND), U10.K13 (GND), U10.K14 (GND), U10.L8 (GND), U10.L9 (GND), U10.L10 (GND), U10.L11 (GND), U10.L12 (GND), U10.L13 (GND), U10.L14 (GND), U10.L18 (GND), U10.M3 (GND), U10.M5 (GND), U10.M8 (GND), U10.M9 (GND), U10.M10 (GND), U10.M11 (GND), U10.M12 (GND), U10.M13 (GND), U10.M14 (GND), U10.N11 (GND), U10.N12 (GND), U10.N13 (GND), U10.N14 (GND), U10.N15 (GND), U10.N18 (GND), U10.P7 (GND), U10.P11 (GND), U10.P12 (GND), U10.P13 (GND), U10.R10 (GND), U10.R18 (GND), U10.T5 (GND), U10.T7 (GND), U10.T13 (GND), U10.V2 (GND), U10.V3 (GND), U10.V4 (GND), U10.V6 (GND), U10.V9 (GND), U10.V12 (GND), U10.V15 (GND), U10.V17 (GND), U10.W1 (GND), U10.W17 (GND), U10.W20 (GND), U10.Y1 (GND), U10.Y2 (GND), U10.Y19 (GND), U10.Y20 (GND), Y4.2 (GND), Y4.4 (GND__1); also elsewhere on the board
unnamed: C94.2, U10.K1 (DXIN), Y4.1 (IN/OUT)
unnamed: C93.2, U10.K2 (DXOUT), Y4.3 (OUT/IN)
unnamed: C91.2, U10.L2 (X32KIN), XTAL1.2
unnamed: C92.2, U10.L3 (X32KOUT), XTAL1.1
VD: U10.G7 (VDD-CPU), U10.G8 (VDD-CPU), U10.G13 (VDD-SYS), U10.G14 (VDD-SYS), U10.H7 (VDD-CPU), U10.H8 (VDD-CPU), U10.H9 (VDD-CPU), U10.H13 (VDD-SYS), U10.H14 (VDD-SYS), U10.J13 (VDD-SYS), U10.J14 (VDD-SYS)

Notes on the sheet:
OUTPUT_Default_Voltage +1V35
OUTPUT_Voltage +1V8
SZQ has no iformation in datasheet
G9 No Description in mentioned in datasheet
